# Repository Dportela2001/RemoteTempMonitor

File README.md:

# RemoteTempMonitor :beers:
Equipo:
 - Diego Alejandro Figueroa del Castillo
 - Danny Esteban Portela Robayo
 - Omar Andrés Cely Villate

Dispositivo embebido enfocado a monitorear y guiar al usuario en la creación de cerveza. Se pretende que el dispositivo funcione como una herramienta de ayuda que pueda facilitar la toma de temperatura, y el subsecuente control de la misma en las fáses de calentamiento y enfriamiento del mosto.

## Descripción no funcional

- Acoplarse adecuadamente al recipiente empleado.
- Comunicarse de manera inalámbrica via Wifi o bluetooth. 
- Tener una resolución de 1°C con incertidumbre de  0.5°C.
- Medir temperaturas entre: 0ºC a 120ºC. 
- Establecer conexiones a mínimo 10 m de distancia.
- Tener un tiempo de comunicación de 15s.

## Descripción funcional 

- Medir temperatura.
- Enviar la temperatura a un dispositivo móvil .
- Permitir la configuración de alarmas de temperatura.
- Disparar alarmas. 
- Mostrar temperatura en un display.

## Fases de la utilización del producto:

## Diagrama de bloques de la solución

## Dispositivos a emplear :page_facing_up:
A continuación se ve una lista resumida de los elementos más importantes a utilizar, con sus respectivos precios, cantidad y tienda sugerida, para una lista más detallada de todos los componentes puede ver el excel [**Lista_componentes.xlsx**](/Lista_componentes.xlsx).

# [Diseño de la pcb](/CircuitDesign):bulb:

Para llevar a cabo el diseño del circuito embebido, se empleó el programa open source Kikad, donde todos los archivos generados se encuentran en la carpeta **CircuitDesign**, en donde se encuentran dos versiones de la placa. La primera empleando vias para conectar la cara superior con la inferior, que se ve en la carpeta **PCB_Design**. Sin embargo, debido a las limitaciones de tiempo y capacidades de realización fue necesario realizar una modificación cambiando las vias por conexiones mediante pines. Este segundo diseño se encuentra en **PCB_Design_Low_Cost**

## Zona de potencia
Como todo circuito electrónico, se requiere de una fuente de potencia para el funcionamiento del mismo. Para esto se planteó fos bloques principales, uno para la regulación de voltage que llega a la ESP32 y sus periféricos, y un bloque de carga para las baterías que alimentan el conjunto. Dichos bloques son:

## Regulador de Voltaje
Dado que la tensión que entregan las baterías de Litio es de 4.2V, es necesario agregar el integrado MIC37303YME, que permite entregar la tensión deseada de 3.3v a la entrada de la ESP32. El esquemático empleado es el siguiente:

## Cargador de Baterías 

Evidentemente las baterias empleadas requieren ser cargadas de vez en cuando para que el sistema funcione. Por ello se agregó el integrado TP4056 con el circuito de la imagen, para realizar esta operación y así mismo proveer de leds guía de cargado y descargado.

Para conveniencia del usuario, se decidió agregar un conector tipo micro-usb B como conector para realizar la carga del dispositivo. Además cuando el dispositivo está sin carga se indicará con un led rojo como se observa a continuación:

En caso de que se haya completado la carga, el indicador resultante es: 

## Esquemático ESP32

El microprocesador empleado para el proyecto es la ESP32 standalone, que posee una flexibilidad y robustez más que suficiente para los propócitos del mismo. Es posible emplear toda la gama de pines GPIO dependiendo de la necesidad, por ejemplo para lectura o escritura. El esquemático resultante es:

Es posible entonces realizar el diseño de la PCB y el ruteo de los caminos  para generar los archivos gerber y enviarlos a impresión en un local dedicado a esta labor. El sieño obtenido finalmente después de añadir además las conexiones entre capas es:

# [Software del dispositivo](/Micropython):snake: 

Para poder programar el microprocesador ESP32 se optó por usar el lenguaje **MicroPython**, por su facilidad de sintaxis, versatilidad y cantidad de librerias disponibles para facilitar el proceso de codificación. Algunas de las librerías empleadas son:

- SH1106 (librería para controlar la pantalla OLED, extraida de: https://github.com/robert-hh/SH1106)
- DS18B20 (librería para controlar la sonda de temperatura, ya presente en Micropython)

Para ver en detalle el código empleado para el funcionamiento del termómetro se puede revisar la carpeta **Micropython** en la rama principal.
Además, se empleó el programa _Mu_ para escribir y subir el código de Micropython directamente a la memoria del ESP32. Otra ventaja de este lenguaje se hace evidente en cuanto a que su subida es veloz al microprocesador, ya que el proceso de compilado del colido ocurre precisamente en este.

## Distintas instancias del programa del proyecto

El programa diseñado para el dispositivo posee distintas instancias tanto de configuración como de funcionamiento, que se encuentran en las siguientes imagenes: 
<table>
  <tr>
      <td></td>
      <td></td>
      <td></td>
   </tr>
</table>

## [Conexión web del dispositivo](/Front-Remotetemp):computer:

Se pretendía realizar la conexión del termómetro con un dispositvo externo con un celular o computadora, con el fin de poder controlar de forma remota las distintas opciones que este ofrece. Sin embargo debido a las limitaciones de tiempo y errores al momento de generar la pagina montada en el servidor, no fue posible terminar de generar esta funcionalidad en el dispositivo. Más si se llego a producir el Front-end de esta parte, la cual se encuentra en la branch **Front-RemoteTemp**, que incluye el archivo _html_, _css_ y _javascrip_. La página diseñada es:

## [Diseño de caja](/Box-Design) :package:

Con el fin de realizar un empaquetado para el termómetro, se realizó el diseño de una caja en madera con corte laser mediante el programa de CorelDraw. El objetivo es que esta  proteja el circuito del termómetro como tal, así como proveerle una mejor apariencia estética. 
Para el diseño se emplearon las medidas tomadas directamente del diseño obtenido de la pcb en Kicad:

Entonces se planea el diseño de tal forma de que haya cierta tolerancia a los tamaños reales de la plata. Se tienen en cuenta elementos que deben ser visibles al usuario como:

- Pantalla de interacción.
- Botonera.
- Puerto de carga USB.
- Led de indicación de bateria baja.
- Led de indicación de carga completa.
- Rejilla para el buzzer.

El resultado del diseño se encuentra en la sección **Box-Design**, donde se encuentran tanto los archivos generados en formatos .pdf y .svg (archivo de gráficos escalables), como el archivo original para ser abierto en el programa CorelDraw. La previsualización resulta:

## Dispositivo resultante 

Después de realizar la soldadura de los elementos en el circuito impreso, se añadieron así mismo los periféricos como la pantalla OLED, el Buzzer y la sonda de temperatura. El dispositivo físico final es el que se ve a continuación:

El layout de los botones y demás periféricos del dispositivo es:

## Conclusiones del proyecto :chart_with_upwards_trend:

- Una correcta planeación de los objetivos del proyecto permite la delimitación del mismo, haciendo que su realización sea más posible.
- El diseño PCB para un sistema embebido requiere de diversas consideraciones, tanto físicas y de funcionamiento como de estandares de producción, para que puedan llegar a ser producidas sin problemas. Estas consideraciones incluyen temas como tamaños de vías, anchos de pista, tamaños de los taladros, grosor del FR4, etc.

## Errores cometidos durante el desarrollo
- Al momento de colocar los pines para colocar la pantalla OLED en el diseño de la placa, se cometió el error de invertir el orden de los pines GND y VDC dado que nos guiamos por la imagen que colocaba el vendedor en su pagina, que era distinta al producto vendido. Esto produjo que la primera parantalla empleada se quemara ya que estaba conectada de manera incorrecta, por lo que fue necesario conseguir otra de estas y realizar una reconexión de manera externa con los sockets para los pines de la pantalla.
- Los tiempos de manufactura de la placa no fueron los adecuados, por lo que fue imposible el solicitar fabricar las PCB en una empreza extrangera China como JLCPCB, PCBWAY, etc. Esto causo que fuera necesario re inventar la placa para no usar vias entre capas, dado que las empresas locales que prestaban estos servicios, lo realizaban a un costo muy alto. Por lo tanto fue necesario recrear la placa de forma en que se omitieran las vías.
- La propia calidad de la placa complicó el hecho de soldar el conector micro-usb, por lo que posteriormente causó una ruptura en el mismo.
- Debido a que no se consiguió desplegar la pagina web en los servidores de _Heroku_ no fue posible crear la lógica de Back-end para poder controlar el dispositivo de forma remota.

# Videos de prueba de funcionamiento
https://user-images.githubusercontent.com/85375999/153422038-b12df55a-1030-432a-aa8d-7aa34144cbf2.mp4

https://user-images.githubusercontent.com/85375999/153430220-765915c4-69fb-4bd9-bc61-4cbe634cb242.mp4

https://user-images.githubusercontent.com/85375999/153430800-7f2c6cfe-6833-4663-b4ba-db0c7dcf290a.mp4

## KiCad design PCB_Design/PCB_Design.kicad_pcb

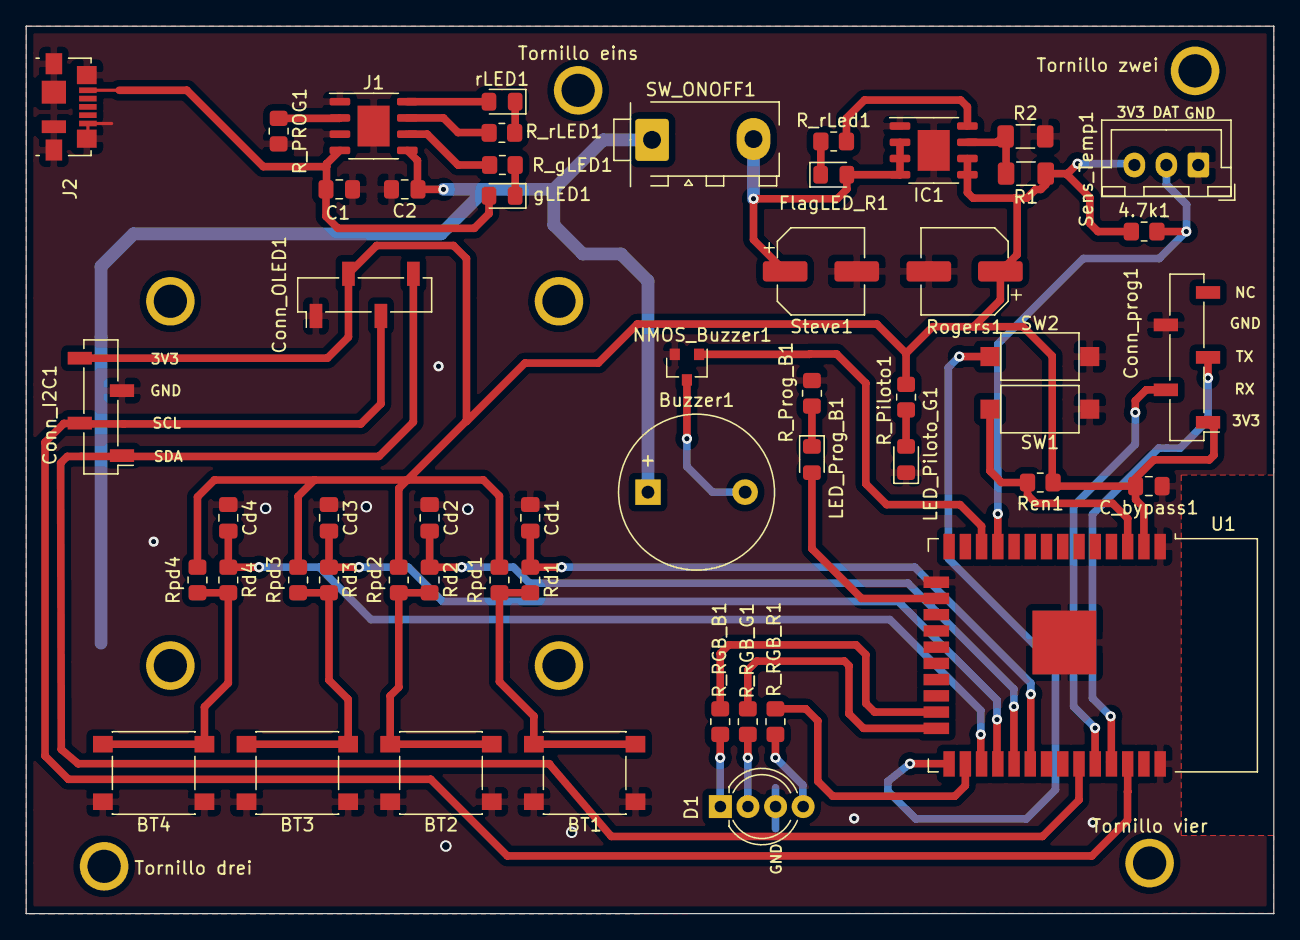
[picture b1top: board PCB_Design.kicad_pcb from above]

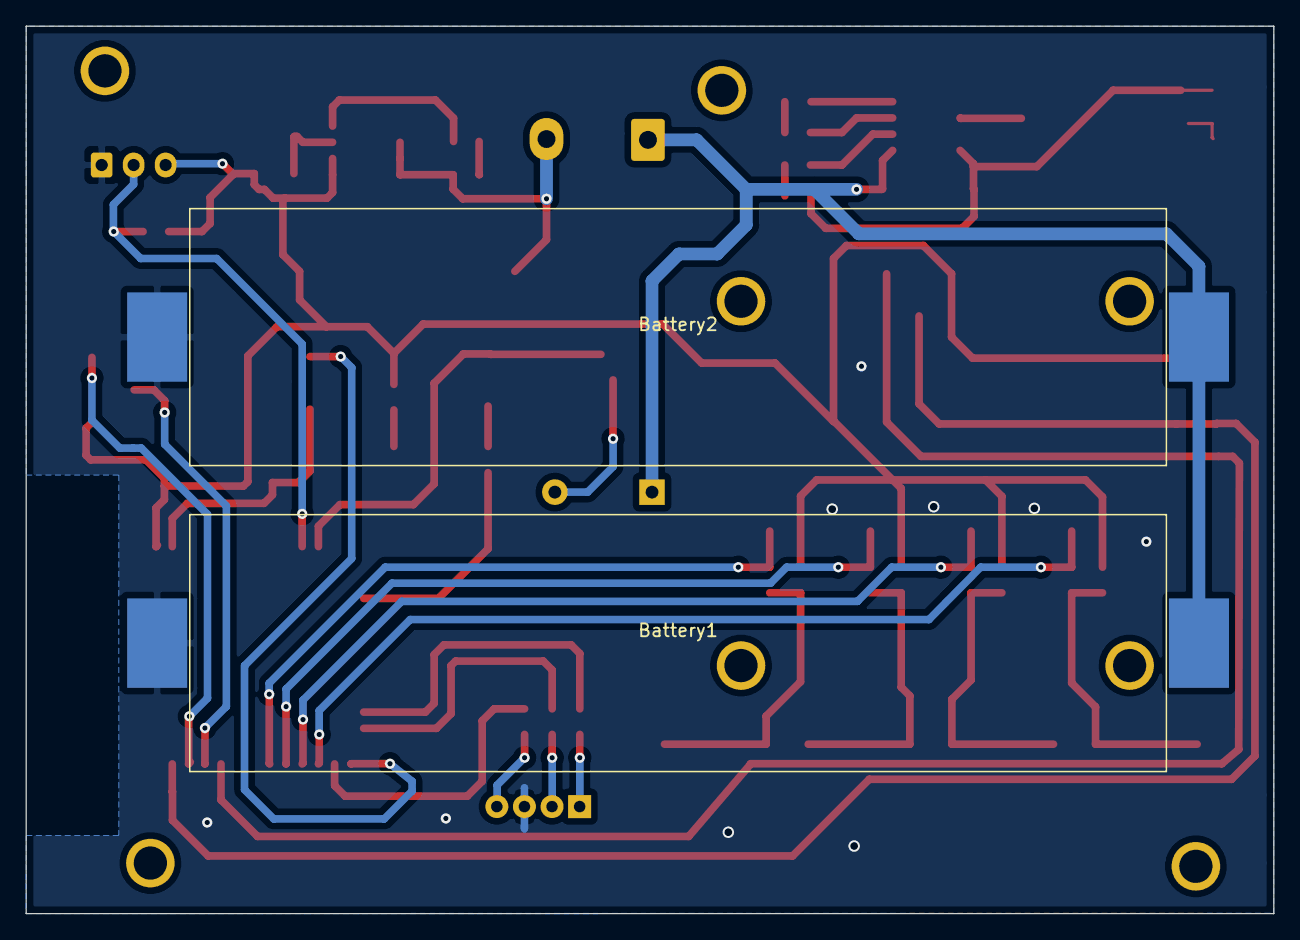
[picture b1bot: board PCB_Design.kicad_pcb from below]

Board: 2 copper layers, 97.6 x 69.4 mm, 59 parts (2 on the bottom side), 40 nets.

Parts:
4.7k1: R_OneWire; R_0805_2012Metric_Pad1.20x1.40mm_HandSolder
BT1, BT2, BT3, BT4: SW_Push; SW_Push_1P1T_NO_6x6mm_H9.5mm
Battery1, Battery2: Battery_Cell; BatteryHolder_MPD_BH-18650-PC2
Buzzer1: Buzzer; Buzzer_12x9.5RM7.6
C1, C2: 10u; C_0805_2012Metric_Pad1.18x1.45mm_HandSolder
C_bypass1: 100pF; C_0805_2012Metric_Pad1.18x1.45mm_HandSolder
Cd1, Cd2, Cd3, Cd4: 0.1u; C_0805_2012Metric_Pad1.18x1.45mm_HandSolder
Conn_I2C1: Conn_01x04_Female; PinSocket_1x04_P2.54mm_Vertical_SMD_Pin1Left
Conn_OLED1: Conn_01x04_Female; PinSocket_1x04_P2.54mm_Vertical_SMD_Pin1Left
Conn_prog1: Conn_01x05_Female; PinSocket_1x05_P2.54mm_Vertical_SMD_Pin1Left
D1: LED_RGBC; LED_D5.0mm-4_RGB_Wide_Pins
FlagLED_R1: LED; LED_0805_2012Metric_Pad1.15x1.40mm_HandSolder
IC1: MIC37303YME; SOIC-8-1EP_3.9x4.9mm_P1.27mm_EP2.514x3.2mm
J1: TP4056; SOIC-8-1EP_3.9x4.9mm_P1.27mm_EP2.514x3.2mm
J2: USB_B_Micro; USB_Micro-B_Molex_47346-0001
LED_Piloto_G1: LED; LED_0805_2012Metric_Pad1.15x1.40mm_HandSolder
LED_Prog_B1: LED; LED_0805_2012Metric_Pad1.15x1.40mm_HandSolder
NMOS_Buzzer1: Q_NMOS_GSD; SOT-23
R1: 6.98k; R_1206_3216Metric_Pad1.30x1.75mm_HandSolder
R2: 4.02k; R_1206_3216Metric_Pad1.30x1.75mm_HandSolder
R_PROG1: 4.7k; R_0805_2012Metric_Pad1.20x1.40mm_HandSolder
R_Piloto1: 180; R_0805_2012Metric_Pad1.20x1.40mm_HandSolder
R_Prog_B1: 47; R_0805_2012Metric_Pad1.20x1.40mm_HandSolder
R_RGB_B1: 47; R_0805_2012Metric_Pad1.20x1.40mm_HandSolder
R_RGB_G1: 47; R_0805_2012Metric_Pad1.20x1.40mm_HandSolder
R_RGB_R1: 180; R_0805_2012Metric_Pad1.20x1.40mm_HandSolder
R_gLED1: 1k; R_0805_2012Metric_Pad1.20x1.40mm_HandSolder
R_rLED1: 1k; R_0805_2012Metric_Pad1.20x1.40mm_HandSolder
R_rLed1: 270; R_0805_2012Metric_Pad1.20x1.40mm_HandSolder
Rd1, Rd2, Rd3, Rd4: 1k; R_0805_2012Metric_Pad1.20x1.40mm_HandSolder
Ren1: 10k; R_0805_2012Metric_Pad1.20x1.40mm_HandSolder
Rogers1: 47u; CP_Elec_6.3x5.9
Rpd1, Rpd2, Rpd3, Rpd4: 10k; R_0805_2012Metric_Pad1.20x1.40mm_HandSolder
SW1, SW2: SW_Push; SW_SPST_CK_RS282G05A3
SW_ONOFF1: SW_Push; TE_MATE-N-LOK_1-770866-x_1x02_P4.14mm_Vertical
Sens_Temp1: DS18B20; JST_XH_B3B-XH-A_1x03_P2.50mm_Vertical
Steve1: 47u; CP_Elec_6.3x5.9
Tornillo drei: MountingHole_2.2mm_M2_DIN965_Pad
Tornillo eins: MountingHole_2.2mm_M2_DIN965_Pad
Tornillo vier: MountingHole_2.2mm_M2_DIN965_Pad
Tornillo zwei: MountingHole_2.2mm_M2_DIN965_Pad
U1: ESP32-WROOM-32
gLED1: LED; LED_0805_2012Metric_Pad1.15x1.40mm_HandSolder
rLED1: LED; LED_0805_2012Metric_Pad1.15x1.40mm_HandSolder

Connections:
/3.3v: 4.7k1.1, C_bypass1.2, Conn_I2C1.4, Conn_OLED1.2, Conn_prog1.1, IC1.5, IC1.6, R1.1, R_Piloto1.1, Ren1.1, Rogers1.1, Rpd1.2, Rpd2.2, Rpd3.2, Rpd4.2, Sens_Temp1.3, U1.2
/Batt: Battery1.1, Battery2.1, Buzzer1.1, C2.1, J1.5, SW_ONOFF1.1
/Button1/Sw: Cd1.2, Rd1.1, U1.30
/Button2 /Sw: Cd2.2, Rd2.1, U1.29
/Button3/Sw: Cd3.2, Rd3.1, U1.28
/Button4/Sw: Cd4.2, Rd4.1, U1.27
GND: BT1.1, BT2.1, BT3.1, BT4.1, Battery1.2, Battery2.2, C1.2, C2.2, C_bypass1.1, Cd1.1, Cd2.1, Cd3.1, Cd4.1, Conn_I2C1.3, Conn_OLED1.1, Conn_prog1.4, D1.3, IC1.1, IC1.9, J1.1, J1.3, J1.9, J2.5, J2.6, LED_Piloto_G1.1, NMOS_Buzzer1.2, R2.2, R_PROG1.2, R_Prog_B1.1, Rogers1.2, SW1.1, SW2.2, Sens_Temp1.1, Steve1.2, U1.1, U1.15, U1.38, U1.39
unnamed: 4.7k1.2, Sens_Temp1.2, U1.11
unnamed: BT1.2, Rd1.2, Rpd1.1
unnamed: BT2.2, Rd2.2, Rpd2.1
unnamed: BT3.2, Rd3.2, Rpd3.1
unnamed: BT4.2, Rd4.2, Rpd4.1
unnamed: Buzzer1.2, NMOS_Buzzer1.3
unnamed: C1.1, J1.4, J2.1, gLED1.2
unnamed: Conn_I2C1.1, Conn_OLED1.4, U1.33
unnamed: Conn_I2C1.2, Conn_OLED1.3, U1.36
unnamed: Conn_prog1.2, U1.34
unnamed: Conn_prog1.3, U1.35
unnamed: D1.1, R_RGB_B1.1
unnamed: D1.2, R_RGB_G1.1
unnamed: D1.4, R_RGB_R1.1
unnamed: FlagLED_R1.1, R_rLed1.1
unnamed: FlagLED_R1.2, IC1.2, IC1.3, IC1.4, SW_ONOFF1.2, Steve1.1
unnamed: IC1.7, R1.2, R2.1
unnamed: IC1.8, R_rLed1.2
unnamed: J1.2, R_PROG1.1
unnamed: J1.6, R_gLED1.1
unnamed: J1.7, R_rLED1.2
unnamed: J1.8, rLED1.2
unnamed: LED_Piloto_G1.2, R_Piloto1.2
unnamed: LED_Prog_B1.1, R_Prog_B1.2
unnamed: LED_Prog_B1.2, U1.16
unnamed: NMOS_Buzzer1.1, U1.12
unnamed: R_RGB_B1.2, U1.23
unnamed: R_RGB_G1.2, U1.24
unnamed: R_RGB_R1.2, U1.26
unnamed: R_gLED1.2, gLED1.1
unnamed: R_rLED1.1, rLED1.1
unnamed: Ren1.2, SW1.2, U1.3
unnamed: SW2.1, U1.25

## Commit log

2021-11-16 Creación del archivo de PCB
2021-11-16 PCB en blanco
2021-11-18 Esquemático del circuito de carga creado, sin formato
2021-11-23 Hojas en el esquemático
    Se añadió como hoja independiente el cargador de la batería al esquemático.
2021-11-23 una pequena prueba + organizacion
2021-11-24 arreglo estetico de esquematico
2021-11-25 Creación de la hoja de regulación de tensión
2021-11-30 Programación por UART-Botones
    Se añadieron los botones con el circuito de debouncing, un botón de enable para la esp32 y los pines para la programacion.
2021-12-01 Partialy finished schematic
2021-12-02 huellas agregadas
2021-12-04 huellas editadas
2021-12-07 Cambio del footprint de los porta baterias
2021-12-09 LCD footprint modified
2021-12-09 Falta tetris
2021-12-09 Nuevas huellas y un poco más de orden
2021-12-09 PCB organizada con casi todo SMD
2021-12-10 un poco mas de aire
2021-12-11 Caminos de la PCB sin GND
2021-12-11 PCB finalizada
2021-12-14 Screws added succesfully
2021-12-15 Creación archivos gerber
2021-12-15 Creación archivos gerber + tornillos pantalla
2021-12-16 PCB diseño fianl retocado + lista componentes
2022-01-04 PCB final con usb B micro, y modelo 3D de la placa
2022-01-12 Lista de componentes casi actualizada
2022-01-12 Lista de componentes actualizada
2022-01-13 PCB terminada
2022-01-20 nueva placa a prueba de la novena
2022-01-21 Actualización última compra en mactrónica
2022-01-21 Actualización con precios de las baterías
2022-01-22 Lista de componentes y precios terminada
2022-01-24 Software folder was created
2022-02-03 Box Files added
2022-02-08 Collection types and user created
2022-02-08 Added WebPage files
2022-02-09 Branches for web development created
    uwu
2022-02-09 CMS branch uptaded
    uwun
2022-02-09 Everything seems updated, I guess
2022-02-09 CMS almost ready, I supose
2022-02-09 Re organize images
2022-02-09 Why do I suck at everything?
2022-02-09 Images Added
2022-02-09 New CMS app, hopefully this is going to work :c
2022-02-09 no quiero commit
2022-02-09 vida setentahijueputa
2022-02-09 fuck
2022-02-09 Last first shit
2022-02-10 Borrando de nuevo
2022-02-10 Added Micropython files
2022-02-10 última vez
2022-04-15 Schematic was created
